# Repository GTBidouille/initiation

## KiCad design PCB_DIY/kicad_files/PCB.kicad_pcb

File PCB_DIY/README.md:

# Design Your First PCB: From Concept to Board

[English version](README_EN.md)

Ce répertoire contient les ressources du workshop.

## Contenu

Vous trouverez dans ce dépôt:

- la présentation du workshop
- les fichiers KiCad
- les fiches techniques (datasheets) du CD4017 et du NE555

## Machines virtuelles

Des machines virtuelles Ubuntu 24.04 avec KiCad sont disponibles:

- une version pour QEMU
- une version pour VirtualBox

Mot de passe: `tototo` ou `totototo`

## Fichiers (cloud)

Lien pour les fichiers:

https://e.pcloud.link/publink/show?code=kZ1pUcZf2nu7QWMclV2N2IoM5SXcha47Rwy

Note importante:

- le clavier est configuré en anglais par défaut
- le clavier français est également installé

## Vidéo de montage

Une petite vidéo pour voir comment souder le montage https://youtu.be/VdpdZ3O2D4w

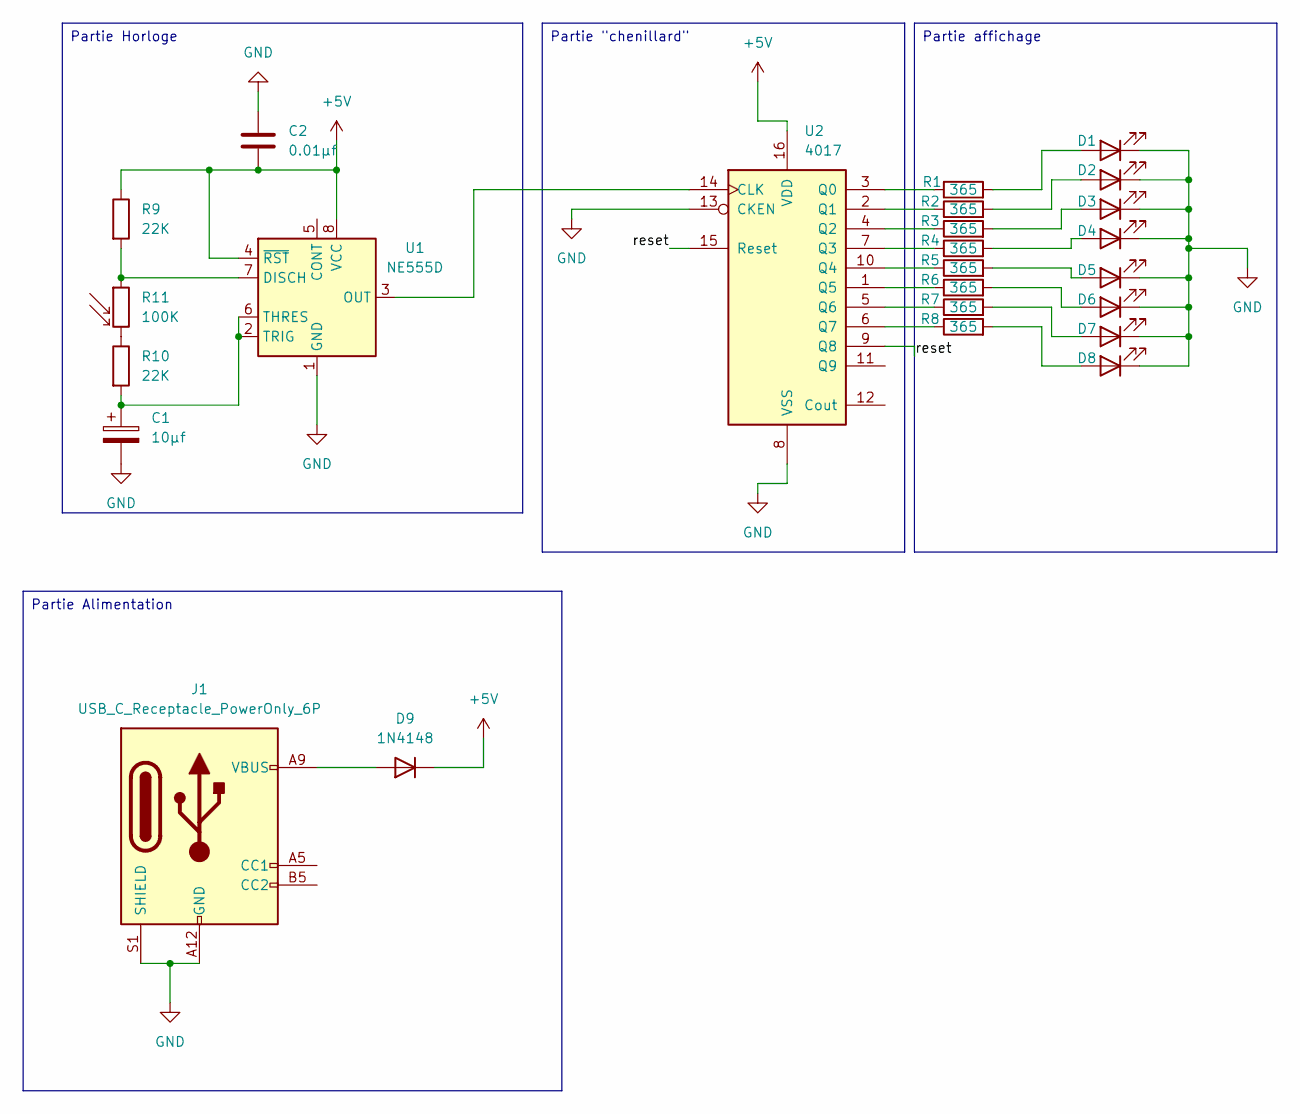
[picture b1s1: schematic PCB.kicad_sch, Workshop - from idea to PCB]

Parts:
C1: 10µf; CP_Radial_D4.0mm_P2.00mm
C2: 0.01µf; C_Disc_D3.0mm_W1.6mm_P2.50mm
D1, D2, D3, D4, D5, D6, D7, D8: LED; LED_D3.0mm
D9: 1N4148; D_DO-35_SOD27_P7.62mm_Horizontal
J1: USB_C_Receptacle_PowerOnly_6P; USB_C_Receptacle_GCT_USB4135-GF-A_6P_TopMnt_Horizontal
R1, R2, R3, R4, R5, R6, R7, R8: 365; R_Axial_DIN0204_L3.6mm_D1.6mm_P7.62mm_Horizontal
R9, R10: 22K; R_Axial_DIN0204_L3.6mm_D1.6mm_P2.54mm_Vertical
R11: 100K; R_LDR_4.9x4.2mm_P2.54mm_Vertical
U1: NE555D; SOIC-8_3.9x4.9mm_P1.27mm
U2: 4017; DIP-16_W7.62mm

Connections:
+5V: C2.2, D9.1 (K), R9.1, U1.4 (~RST), U1.8 (VCC), U2.16 (VDD)
/reset: U2.9 (Q8), U2.15 (Reset)
GND: C1.2, C2.1, D1.1 (K), D2.1 (K), D3.1 (K), D4.1 (K), D5.1 (K), D6.1 (K), D7.1 (K), D8.1 (K), J1.A12 (GND), J1.B12 (GND), J1.S1 (SHIELD), U1.1 (GND), U2.8 (VSS), U2.13 (CKEN)
unnamed: D1.2 (A), R1.2
unnamed: D2.2 (A), R2.2
unnamed: D3.2 (A), R3.2
unnamed: D4.2 (A), R4.2
unnamed: D5.2 (A), R5.2
unnamed: D6.2 (A), R6.2
unnamed: D7.2 (A), R7.2
unnamed: D8.2 (A), R8.2
unnamed: D9.2 (A), J1.A9 (VBUS), J1.B9 (VBUS)
unnamed: R10.1, R11.2
unnamed: R9.2, R11.1, U1.7 (DISCH)
unnamed: U1.3 (OUT), U2.14 (CLK)
unnamed: C1.1, R10.2, U1.2 (TRIG), U1.6 (THRES)
unnamed: R1.1, U2.3 (Q0)
unnamed: R2.1, U2.2 (Q1)
unnamed: R3.1, U2.4 (Q2)
unnamed: R4.1, U2.7 (Q3)
unnamed: R5.1, U2.10 (Q4)
unnamed: R6.1, U2.1 (Q5)
unnamed: R7.1, U2.5 (Q6)
unnamed: R8.1, U2.6 (Q7)

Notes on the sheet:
Partie affichage
Partie Alimentation
Partie "chenillard"
Partie Horloge

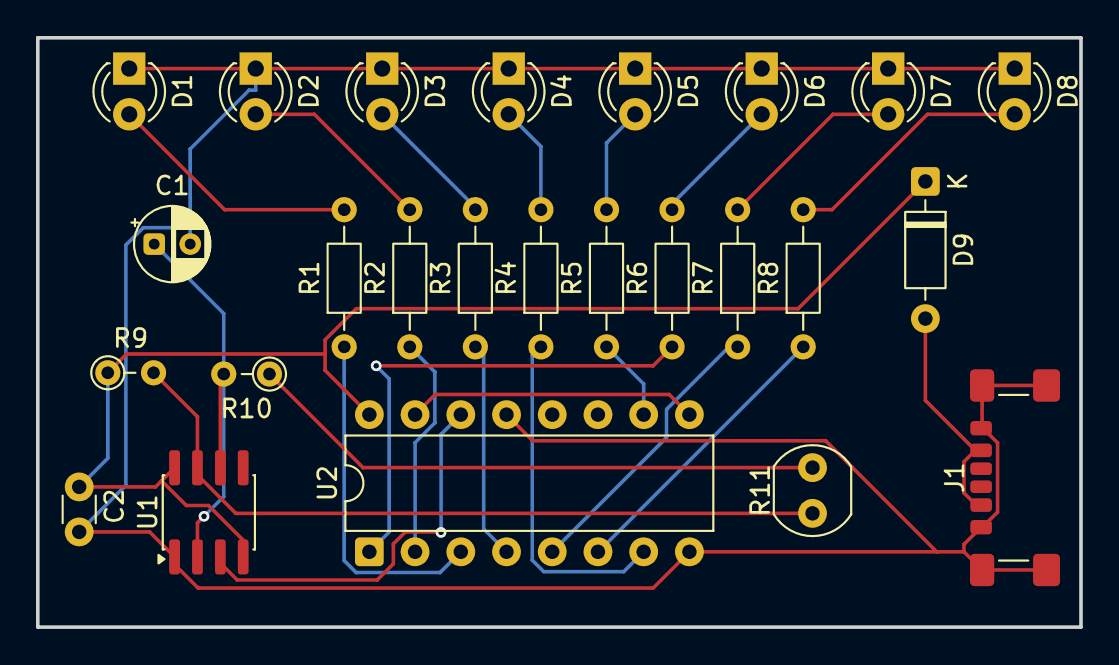
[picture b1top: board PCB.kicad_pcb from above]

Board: 2 copper layers, 57.9 x 32.7 mm, 25 parts (0 on the bottom side), 24 nets.
